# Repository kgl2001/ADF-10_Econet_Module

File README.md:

# ADF-10 Style Econet module for Acorn computers
A fully compatible through hole version of the original Acorn ADF-10 Econet module.

Some general notes:

* Suitable for use with any Acorn Master series, Archimedes series and other devices that would accept the original Acorn ADF-10 Econet module.
* The dimensions of the module differ very slightly from the original ADF-10 module. Instead, it matches the outline of the Raspberry Pi models 2, 3 & 4 and has been specifically designed to fit on other PCBs (eg PiEconetBridge V1) that are designed to work the the Raspberry Pi.
* The source files are to be used with KiCAD v9.0.0 or later.
* The gerber files have been optimised for fabrication by JLCPCB. In particular, there is a 8mmx8mm silkscreen box on the rear of the PCB. This is to allow a 2D barcode, with unique serial number to be printed on the PCB.
* If you want the barcode to be added, then make sure to select this option in the 'Mark on PCB' field, and make sure to select 'Specify position' in the '2D Barcode Position' field, otherwise you will end up with a white 8mm x 8mm box printed on your PCB and a 8mm x 8mm barcode printed at a position of JLCPCBs choosing. Thrust me on this!
* If you don't want the barcode added, then remove the 8mm x 8mm box from the silkscreen layer and regenerate the gerbers. Otherwise you will end up with a white 8mm x 8mm box printed on your PCB.

Please refer to the following discussion on Stardot for further details: https://stardot.org.uk/forums/viewtopic.php?p=327138#p327138

## Author

The Mini Econet module is developed and maintained by Ken Lowe.
    
## Hardware License (Creative Commons BY-SA 4.0)

Please see the following link for details: https://creativecommons.org/licenses/by-sa/4.0/

You are free to:

Share - copy and redistribute the material in any medium or format
Adapt - remix, transform, and build upon the material
for any purpose, even commercially.

This license is acceptable for Free Cultural Works.

The licensor cannot revoke these freedoms as long as you follow the license terms.

Under the following terms:

Attribution - You must give appropriate credit, provide a link to the license, and indicate if changes were made. You may do so in any reasonable manner, but not in any way that suggests the licensor endorses you or your use.

ShareAlike - If you remix, transform, or build upon the material, you must distribute your contributions under the same license as the original.

No additional restrictions - You may not apply legal terms or technological measures that legally restrict others from doing anything the license permits.

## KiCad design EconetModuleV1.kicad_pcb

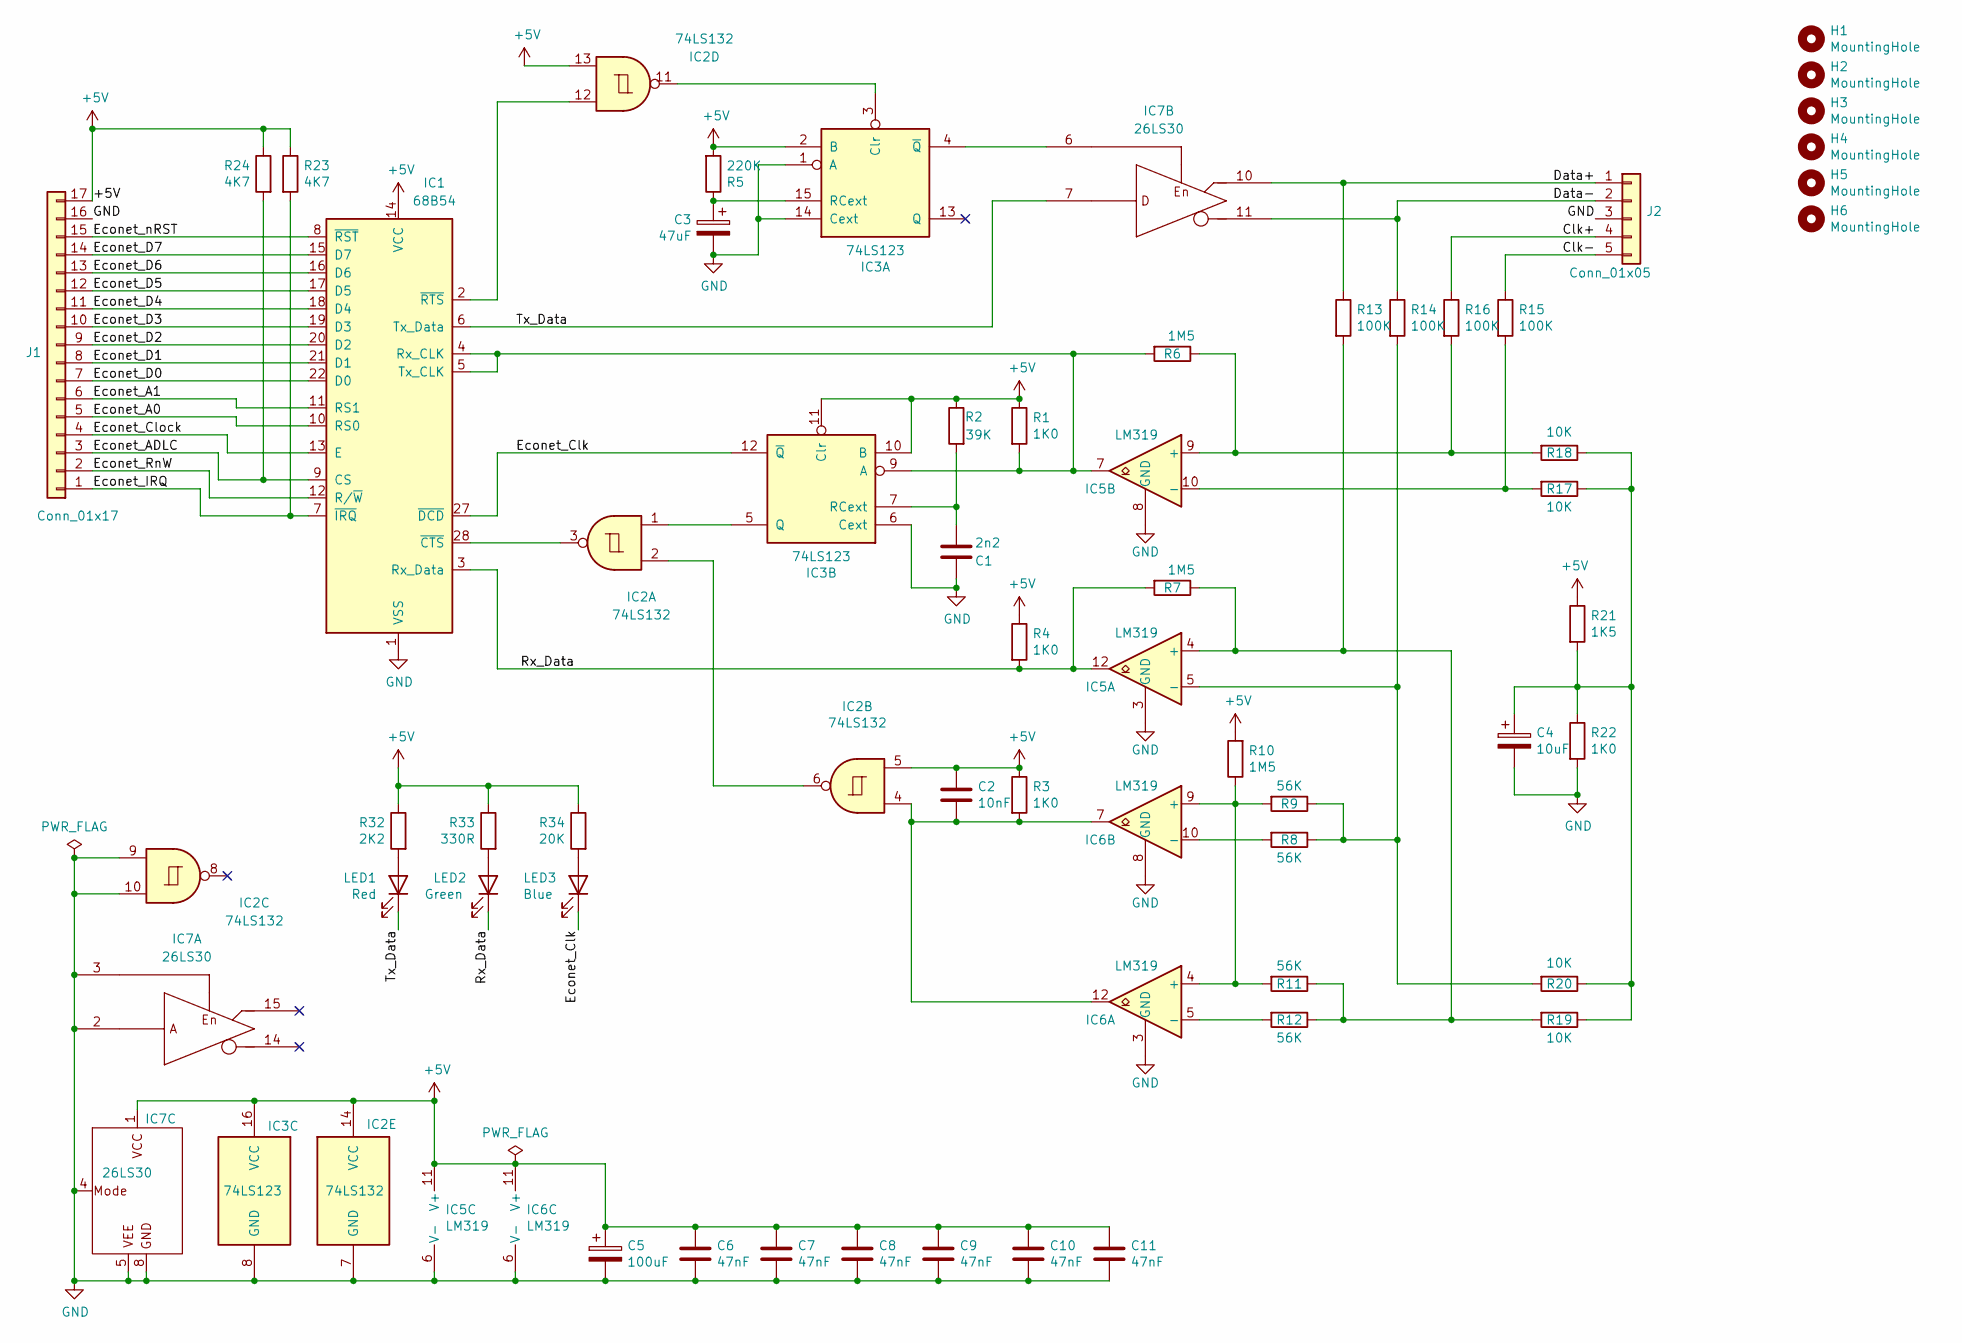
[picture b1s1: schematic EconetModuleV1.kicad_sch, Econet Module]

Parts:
C1: 2n2; C_Disc_D4.3mm_W1.9mm_P5.00mm
C2: 10nF; C_Disc_D4.3mm_W1.9mm_P5.00mm
C3: 47uF; CP_Radial_Tantal_D6.0mm_P2.50mm
C4: 10uF; CP_Radial_D5.0mm_P2.00mm
C5: 100uF; CP_Radial_D5.0mm_P2.00mm
C6, C7, C8, C9, C10, C11: 47nF; C_Rect_L7.2mm_W2.5mm_P5.00mm_FKS2_FKP2_MKS2_MKP2
H1, H2, H3, H4: MountingHole; MountingHole_2.7mm
H5, H6: MountingHole; MountingHole_4mm
IC1: 68B54; DIP-28_W15.24mm
IC2: 74LS132; DIP-14_W7.62mm
IC3: 74LS123; DIP-16_W7.62mm
IC5, IC6: LM319; DIP-14_W7.62mm
IC7: 26LS30; DIP-16_W7.62mm
J1: Conn_01x17; PinHeader_1x17_P2.54mm_Vertical
J2: Conn_01x05; PinHeader_1x05_P2.54mm_Vertical
LED1: Red; LED_D3.0mm
LED2: Green; LED_D3.0mm
LED3: Blue; LED_D3.0mm
R1, R3, R4, R22: 1K0; R_Axial_DIN0207_L6.3mm_D2.5mm_P10.16mm_Horizontal
R2: 39K; R_Axial_DIN0207_L6.3mm_D2.5mm_P10.16mm_Horizontal
R5: 220K; R_Axial_DIN0207_L6.3mm_D2.5mm_P10.16mm_Horizontal
R6, R7, R10: 1M5; R_Axial_DIN0207_L6.3mm_D2.5mm_P10.16mm_Horizontal
R8, R9, R11, R12: 56K; R_Axial_DIN0207_L6.3mm_D2.5mm_P10.16mm_Horizontal
R13, R14, R15, R16: 100K; R_Axial_DIN0207_L6.3mm_D2.5mm_P10.16mm_Horizontal
R17, R18, R19, R20: 10K; R_Axial_DIN0207_L6.3mm_D2.5mm_P10.16mm_Horizontal
R21: 1K5; R_Axial_DIN0207_L6.3mm_D2.5mm_P10.16mm_Horizontal
R23, R24: 4K7; R_Axial_DIN0207_L6.3mm_D2.5mm_P10.16mm_Horizontal
R32: 2K2; R_Axial_DIN0207_L6.3mm_D2.5mm_P10.16mm_Horizontal
R33: 330R; R_Axial_DIN0207_L6.3mm_D2.5mm_P10.16mm_Horizontal
R34: 20K; R_Axial_DIN0207_L6.3mm_D2.5mm_P10.16mm_Horizontal

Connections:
+5V: C2.1, C5.1, C6.1, C7.1, C8.1, C9.1, C10.1, C11.1, IC1.14 (VCC), IC2.5, IC2.13, IC2.14 (VCC), IC3.2 (B), IC3.10 (B), IC3.11 (Clr), IC3.16 (VCC), IC5.11 (V+), IC6.11 (V+), IC7.1 (VCC), J1.17, R1.1, R2.1, R3.1, R4.1, R5.2, R10.2, R21.1, R23.1, R24.1, R32.1, R33.1, R34.1
/Clk+: J2.4, R16.1
/Clk-: J2.5, R15.1
/Data+: IC7.10 (OutD), J2.1, R13.1
/Data-: IC7.11 (OutC), J2.2, R14.1
/Econet_A0: IC1.10 (RS0), J1.5
/Econet_A1: IC1.11 (RS1), J1.6
/Econet_ADLC: IC1.9 (CS), J1.3, R24.2
/Econet_Clk: IC1.27 (~DCD), IC3.12 (~Q), LED3.1 (K)
/Econet_Clock: IC1.13 (E), J1.4
/Econet_D0: IC1.22 (D0), J1.7
/Econet_D1: IC1.21 (D1), J1.8
/Econet_D2: IC1.20 (D2), J1.9
/Econet_D3: IC1.19 (D3), J1.10
/Econet_D4: IC1.18 (D4), J1.11
/Econet_D5: IC1.17 (D5), J1.12
/Econet_D6: IC1.16 (D6), J1.13
/Econet_D7: IC1.15 (D7), J1.14
/Econet_IRQ: IC1.7 (~IRQ), J1.1, R23.2
/Econet_RnW: IC1.12 (R/~W), J1.2
/Econet_nRST: IC1.8 (~RST), J1.15
/Rx_Data: IC1.3 (Rx_Data), IC5.12, LED2.1 (K), R4.2, R7.2
/Tx_Data: IC1.6 (Tx_Data), IC7.7 (InputD), LED1.1 (K)
GND: C1.1, C3.2, C4.2, C5.2, C6.2, C7.2, C8.2, C9.2, C10.2, C11.2, IC1.1 (VSS), IC2.7 (GND), IC2.9, IC2.10, IC3.1 (A), IC3.6 (Cext), IC3.8 (GND), IC3.14 (Cext), IC5.3 (GND), IC5.6 (V-), IC5.8 (GND), IC6.3 (GND), IC6.6 (V-), IC6.8 (GND), IC7.2 (InputA), IC7.3 (/EnableAB), IC7.4 (Mode), IC7.5 (GND), IC7.8 (VEE), J1.16, J2.3, R22.2
unnamed: C2.2, IC2.4, IC6.7, IC6.12, R3.2
unnamed: C4.1, R17.1, R18.1, R19.1, R20.1, R21.2, R22.1
unnamed: IC1.4 (Rx_CLK), IC1.5 (Tx_CLK), IC3.9 (A), IC5.7, R1.2, R6.2
unnamed: IC1.28 (~CTS), IC2.3
unnamed: IC1.2 (~RTS), IC2.12
unnamed: IC2.2, IC2.6
unnamed: IC2.11, IC3.3 (Clr)
unnamed: C3.1, IC3.15 (RCext), R5.1
unnamed: IC3.4 (~Q), IC7.6 (EnableCD)
unnamed: IC2.1, IC3.5 (Q)
unnamed: C1.2, IC3.7 (RCext), R2.2
unnamed: IC5.4 (+), R7.1, R11.1, R12.1, R13.2, R19.2
unnamed: IC5.5 (-), R8.1, R9.1, R14.2, R20.2
unnamed: IC5.9 (+), R6.1, R16.2, R18.2
unnamed: IC5.10 (-), R15.2, R17.2
unnamed: IC6.4 (+), IC6.9 (+), R9.2, R10.1, R11.2
unnamed: IC6.5 (-), R12.2
unnamed: IC6.10 (-), R8.2
unnamed: LED1.2 (A), R32.2
unnamed: LED2.2 (A), R33.2
unnamed: LED3.2 (A), R34.2

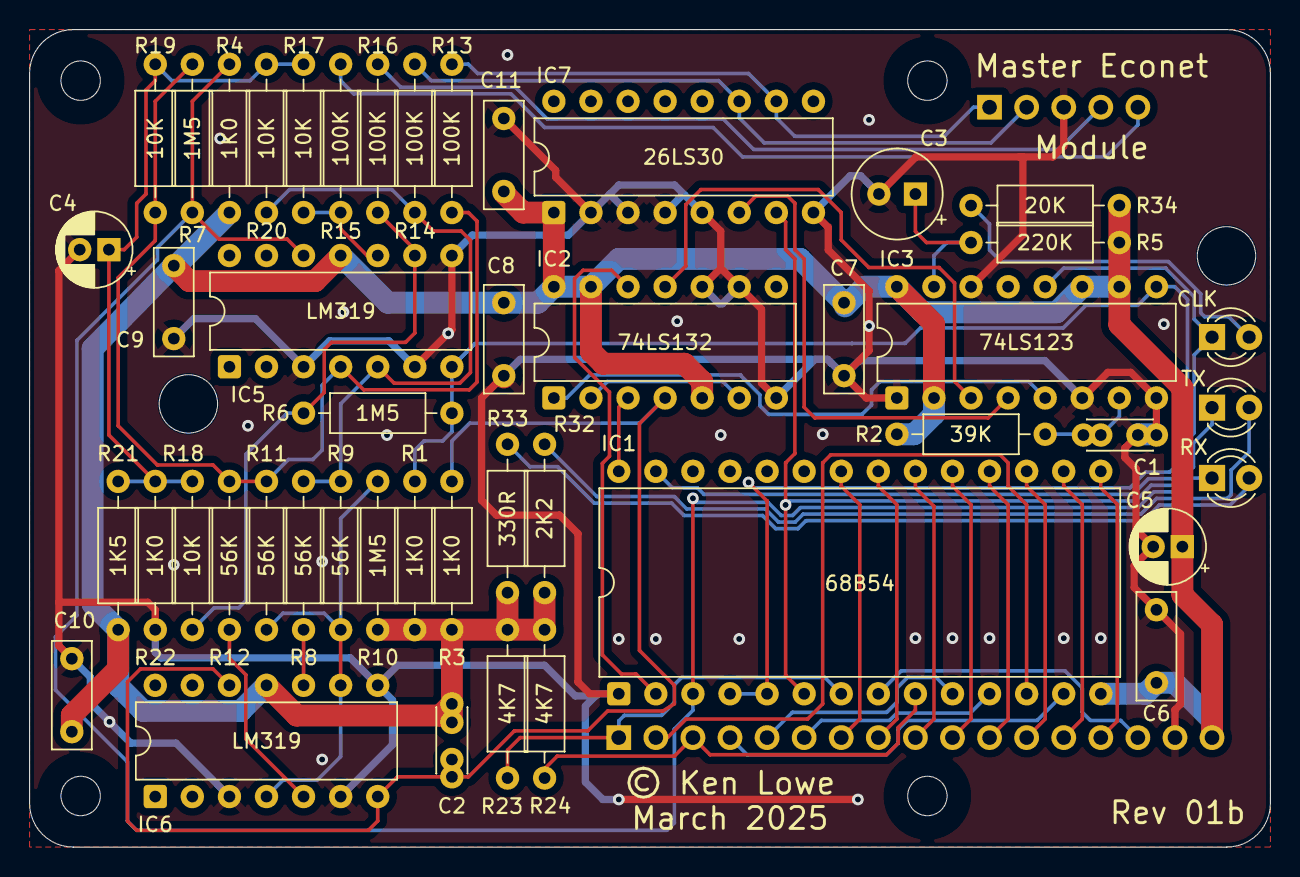
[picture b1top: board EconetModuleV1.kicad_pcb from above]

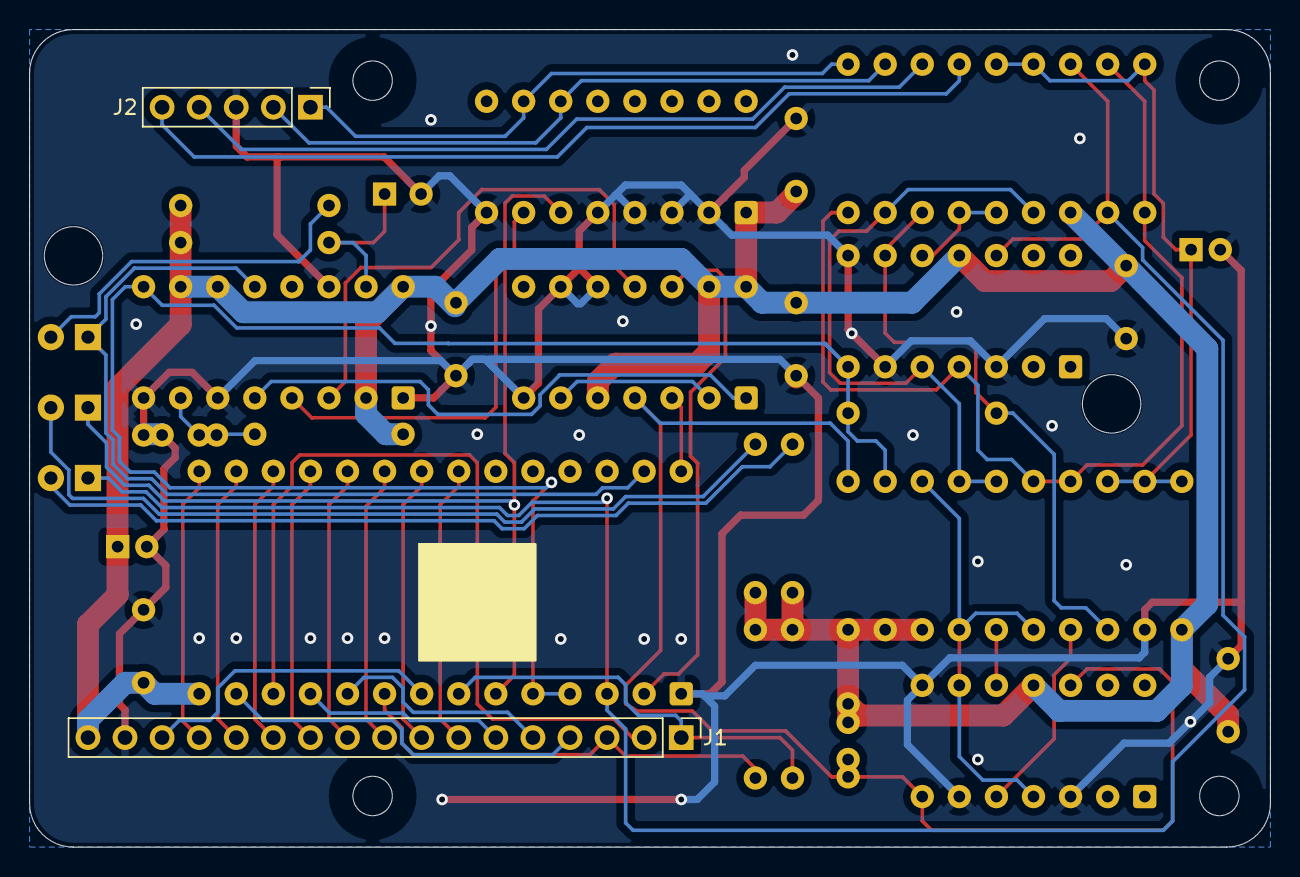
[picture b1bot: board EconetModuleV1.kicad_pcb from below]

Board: 2 copper layers, 85.0 x 56.0 mm, 55 parts (2 on the bottom side), 45 nets.

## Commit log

2025-05-19 Add License
2025-05-19 Add ReadMe

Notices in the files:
EconetModuleV1.kicad_pcb:
© Ken Lowe
